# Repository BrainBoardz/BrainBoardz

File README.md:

### 

## BRAINBOARDZ - PLUG and CODE! 

This is the official repository for the BrainBoardz BZBoard system. BZBoards are ESP32-S3 and RP2350B based video (DVI/VGA) and audio centric microcontroller computers. They support Arduino, CircuitPython, MicroPython, AnnexRDS and PlatformIO. Our mission is to empower designers to develop projects based on our advanced and powerful microcontroller architecture. The entire BrainBoardz system is fully documented abd open source. The PCB designs and schematics for all BrainBoardz hardware is released under the CERN-OHL-W V2 license. All software and firmware is released under the GNU GPLv3 License. 

Through the use of our expanding range of cross compatible modules and easy prototyping boards anyone can easily develop custom projects to harness the impressive capabilities of the Raspberry Pi RP2350B and the Espressif ESP32-S3. The boards are specifically designed to be easily adaptable to retro-PC projects. Simply connect one of our ESP32-S3 or RP235OB boards to a USB cable and you are ready to go. 

We do not permit 3rd party board developers to use our logo/branding (as per CERN-OHL-W V2), but you are welcome to indicate that your project is BrainBoardz compatible if it is 100% (pin) compatible and it is produced using lead free solder.  The PCB designs and schematics for all BrainBoardz hardware is released under the CERN-OHL-W V2 license. All software and firmware is released under the GNU GPLv3 License. 

***

Firmware Notes: 

The ESP32S3 Zushi board supports Arduino and AnnexRDS. The RP2350B Beanz board supports CircuitPython, Micropython, Arduino and PlaformIO. For further instructions on these platforms please visit the Downloads page of the BrainBoardz website at:

https://www.brainboardz.com/downloads/

Plug and Code! 

<!--
**BrainBoardz/BrainBoardz** is a ✨ _special_ ✨ repository because its `README.md` (this file) appears on your GitHub profile.

-->

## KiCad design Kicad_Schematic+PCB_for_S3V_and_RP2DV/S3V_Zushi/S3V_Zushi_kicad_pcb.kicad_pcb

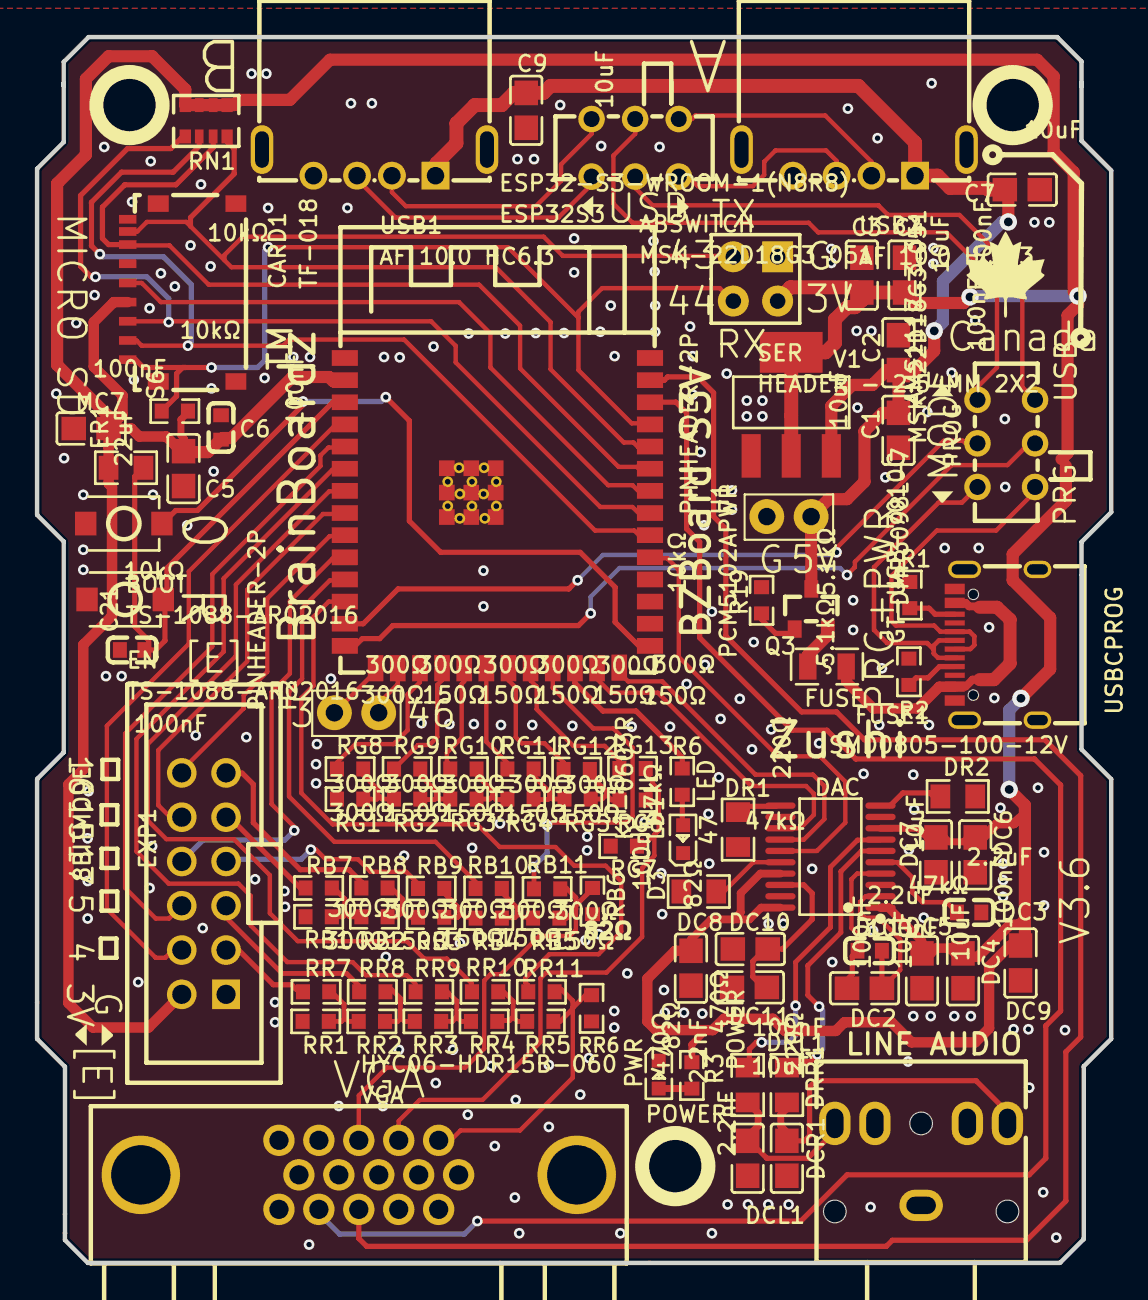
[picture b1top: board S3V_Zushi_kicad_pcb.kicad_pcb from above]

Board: 2 copper layers, 61.6 x 70.3 mm, 107 parts (0 on the bottom side), 84 nets.

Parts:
ABSWITCH: MSK-22D18G3 051; SW-TH_HX-MSK-22D18G3-051
AUS: PJ-3062-G; AUDIO-TH_PJ-3062-G
BOOT: TS-1088-AR02016; SW-SMD_L3.9-W3.0-P4.45
C1, C3, C7, C9: 10uF; C0805
C2, C4: 100nF; C0805
C5: 22uF; C0805
C6, C21: 100nF; C0603
CARD1: TF-018; TF-SMD_TF-018
D3: 47kΩ; R0805
DAC: PCM5102APWR; TSSOP-20_L6.5-W4.4-P0.65-LS6.4-BL
DC1, DC3: 2.2uF; C0603
DC2, DC5, DC7, DC8, DC10: 100nF; C0805
DC4, DC6, DC9, DC11: 10uF; C0805
DCL1: 2.2nF; C0805
DCR1: 2.2nF; C0805
DR1, DR2: 47kΩ; R0805
DRL1: 470Ω; R0805
DRR1: 470Ω; R0805
EN: TS-1088-AR02016; SW-SMD_L3.9-W3.0-P4.45
ER1: 10kΩ; R0805
ESP32S3: ESP32-S3-WROOM-1(N8R8); WIRELM-SMD_ESP32-S3-WROOM-1
EXP1: 8BITMODE; IDC-TH_12P-P2.54_BOOMELE-2X6P-2.54MM
FUSE1: SMD0805-100-12V; F0805
H1, H2: PINHEADER-2P; CONNECTOR_PINHEADER_2.54MM{colon}PINHEADER_1X11_P_2.54MM
Hole_gge1593659: Hole_gge1593659
Hole_gge2213095: Hole_gge2213095
Hole_gge3207251: Hole_gge3207251
LD1: KT-0603R; LED0603-RD
MC7: 100nF; C0805
PROG: MSK-22D18G3 051; SW-TH_HX-MSK-22D18G3-051
PWR: POWER; LED0603-RD
Pad_gge1239083: Pad_gge1239083
Pad_gge1239086: Pad_gge1239086
Pad_gge1239089: Pad_gge1239089
Pad_gge1239092: Pad_gge1239092
Pad_gge1239095: Pad_gge1239095
Pad_gge1239098: Pad_gge1239098
Pad_gge1239101: Pad_gge1239101
Pad_gge1239104: Pad_gge1239104
Pad_gge1239107: Pad_gge1239107
Pad_gge1239110: Pad_gge1239110
Pad_gge1239113: Pad_gge1239113
Pad_gge1239116: Pad_gge1239116
Q3: DMP3098L-7; SOT-23_L2.9-W1.3-P1.90-LS2.4-BR
R1, R2: 5.1kΩ; R0603
R3, R6: 220Ω; R0603
R19: 10kΩ; R0603
RB1, RB7, RB8, RB9, RB10, RB11: 300Ω; R0603
RB2, RB3, RB4, RB5: 150Ω; R0603
RB6: 82Ω; R0603
RG1, RG8, RG9, RG10, RG11, RG12, RG13: 300Ω; R0603
RG2, RG3, RG4, RG5, RG6: 150Ω; R0603
RG7: 82Ω; R0603
RN1: 10kΩ; RES-ARRAY-SMD_0603-8P-L3.2-W1.6-BL
RR1, RR7, RR8, RR9, RR10, RR11: 300Ω; R0603
RR2, RR3, RR4, RR5: 150Ω; R0603
RR6: 82Ω; R0603
S6: 10kΩ; R0603
SER: HEADER - 2.54MM 2X2; 2X2X2.54MM HEADER
USB1, USB2: AF 10.0 HC6.3; USB-A-TH_AF-10.0-HC6.3
USBCPROG: GT-USB-7010C; USB-C-SMD_GT-USB-7010C
V1: AMS1117-3.3; SOT-223-3_L6.5-W3.4-P2.30-LS7.0-BR
VGA: HYC06-HDR15B-060; DSUB-TH_HYC06-HDR15B-060

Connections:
3.3V: C3.2, C4.2, C5.2, C6.2, CARD1.4, DAC.1, DAC.8, DAC.17, DAC.20, DC4.2, DC5.2, DC6.2, DC7.1, DC8.2, DC9.2, ER1.2, ESP32S3.2, EXP1.2, MC7.2, R3.1, RN1.1, RN1.2, RN1.3, RN1.4, S6.2, SER.3, V1.2, V1.4
+5V: C1.2, C2.2, C7.1, C9.1, H1.2, Q3.3, USB1.1, USB2.1, V1.3
AD+: ABSWITCH.1, USB2.3
AD-: ABSWITCH.4, USB2.2
BD+: ABSWITCH.3, USB1.3
BD-: ABSWITCH.6, USB1.2
BLUE: RB5.2, RB6.1, RB11.2, VGA.3
BOOT: BOOT.1, ESP32S3.27
D1+: PROG.4, USBCPROG.A6, USBCPROG.B6
D1-: PROG.1, USBCPROG.A7, USBCPROG.B7
D3_2: D3.2, DAC.16
DC2_1: DAC.4, DC1.1, DC2.1
DC2_2: DAC.2, DC1.2, DC2.2
DC3_1: DAC.5, DC3.1
DC10_1: DAC.18, DC10.1, DC11.1
DR1_2: DAC.11, DR1.2
DR2_2: DAC.10, DR2.2
EN: C21.1, EN.1, ER1.1, ESP32S3.3
G3: ESP32S3.15, H2.1
G4: ESP32S3.4, EXP1.4
G4VGA: EXP1.3, RR7.1
G5: ESP32S3.5, EXP1.6
G5VGA: EXP1.5, RR8.1
G6: ESP32S3.6, RR9.1
G7: ESP32S3.7, RR10.1
G8: ESP32S3.12, RR11.1
G9: ESP32S3.17, RG8.1
G10: ESP32S3.18, RG9.1
G11: ESP32S3.19, RG10.1
G12: ESP32S3.20, RG11.1
G13: ESP32S3.21, RG12.1
G14: ESP32S3.22, RG13.1
G15: ESP32S3.8, EXP1.10
G15VGA: EXP1.9, RB7.1
G16: ESP32S3.9, EXP1.12
G16VGA: EXP1.11, RB8.1
G17: ESP32S3.10, EXP1.8
G17VGA: EXP1.7, RB9.1
G18: ESP32S3.11, RB10.1
G19: ESP32S3.13, PROG.2
G20: ESP32S3.14, PROG.5
G21: ESP32S3.23, RB11.1
G38: DAC.15, ESP32S3.31
G39: CARD1.2, ESP32S3.32, RN1.6
G40: CARD1.3, ESP32S3.33, RN1.5
G41: CARD1.5, ESP32S3.34
G42: CARD1.7, ESP32S3.35, RN1.7
G43: CARD1.8, ESP32S3.36, RN1.8, SER.2
G44: CARD1.1, ESP32S3.37, S6.1, SER.4
G45: DAC.14, ESP32S3.26
G46: ESP32S3.16, H2.2
G47: ESP32S3.24, R6.1
G48: DAC.13, ESP32S3.25
GND: AUS.1, BOOT.2, C1.1, C2.1, C3.1, C4.1, C5.1, C6.1, C7.2, C9.2, C21.2, CARD1.6, CARD1.10, DAC.3, DAC.9, DAC.12, DAC.19, DC3.2, DC4.1, DC5.1, DC6.1, DC7.2, DC8.1, DC9.1, DC10.2, DC11.2, DCL1.1, DCR1.1, DR1.1, DR2.1, EN.2, ESP32S3.1, ESP32S3.40, ESP32S3.41, EXP1.1, H1.1, LD1.1, MC7.1, PWR.1, Pad_gge1239083.43, Pad_gge1239086.43, Pad_gge1239089.43, Pad_gge1239092.43, Pad_gge1239095.43, Pad_gge1239098.43, Pad_gge1239101.43, Pad_gge1239104.43, Pad_gge1239107.43, Pad_gge1239110.43, Pad_gge1239113.43, Pad_gge1239116.43, R1.2, R2.2, R19.2, RB1.1, RB6.2, RG1.1, RG7.2, RR1.1, RR6.2, SER.1, USB1.4, USB1.5, USB1.6, USB2.4, USB2.5, USB2.6, USBCPROG.1, USBCPROG.2, USBCPROG.3, USBCPROG.4, USBCPROG.A1B12, USBCPROG.B1A12, V1.1, VGA.5, VGA.6, VGA.7, VGA.8, VGA.10, VGA.16, VGA.17
GREEN: RG6.2, RG7.1, RG13.2, VGA.2
HSYNC: ESP32S3.39, VGA.13
OUTL: AUS.2, DCL1.2, DRL1.1
OUTLS: DAC.6, DRL1.2
OUTR: AUS.5, DCR1.2, DRR1.1
OUTRS: DAC.7, DRR1.2
Q3_1: Q3.1, R19.1
R3_2: PWR.2, R3.2
R6_2: LD1.2, R6.2
RB1_2: RB1.2, RB2.1, RB7.2
RB2_2: RB2.2, RB3.1, RB8.2
RB3_2: RB3.2, RB4.1, RB9.2
RB4_2: RB4.2, RB5.1, RB10.2
RED: RR5.2, RR6.1, RR11.2, VGA.1
RG1_2: RG1.2, RG2.1, RG8.2
RG2_2: RG2.2, RG3.1, RG9.2
RG3_2: RG3.2, RG4.1, RG10.2
RG4_2: RG4.2, RG5.1, RG11.2
RG5_2: RG5.2, RG6.1, RG12.2
RR1_2: RR1.2, RR2.1, RR7.2
RR8_2: RR2.2, RR3.1, RR8.2
RR9_2: RR3.2, RR4.1, RR9.2
RR10_2: RR4.2, RR5.1, RR10.2
UD+: ABSWITCH.2, PROG.6
UD-: ABSWITCH.5, PROG.3
USBCPROG_A5: R2.1, USBCPROG.A5
USBCPROG_B5: R1.1, USBCPROG.B5
VSYNC: ESP32S3.38, VGA.14
VUSB: FUSE1.1, USBCPROG.A4B9, USBCPROG.B4A9
VUSBPF: FUSE1.2, Q3.2

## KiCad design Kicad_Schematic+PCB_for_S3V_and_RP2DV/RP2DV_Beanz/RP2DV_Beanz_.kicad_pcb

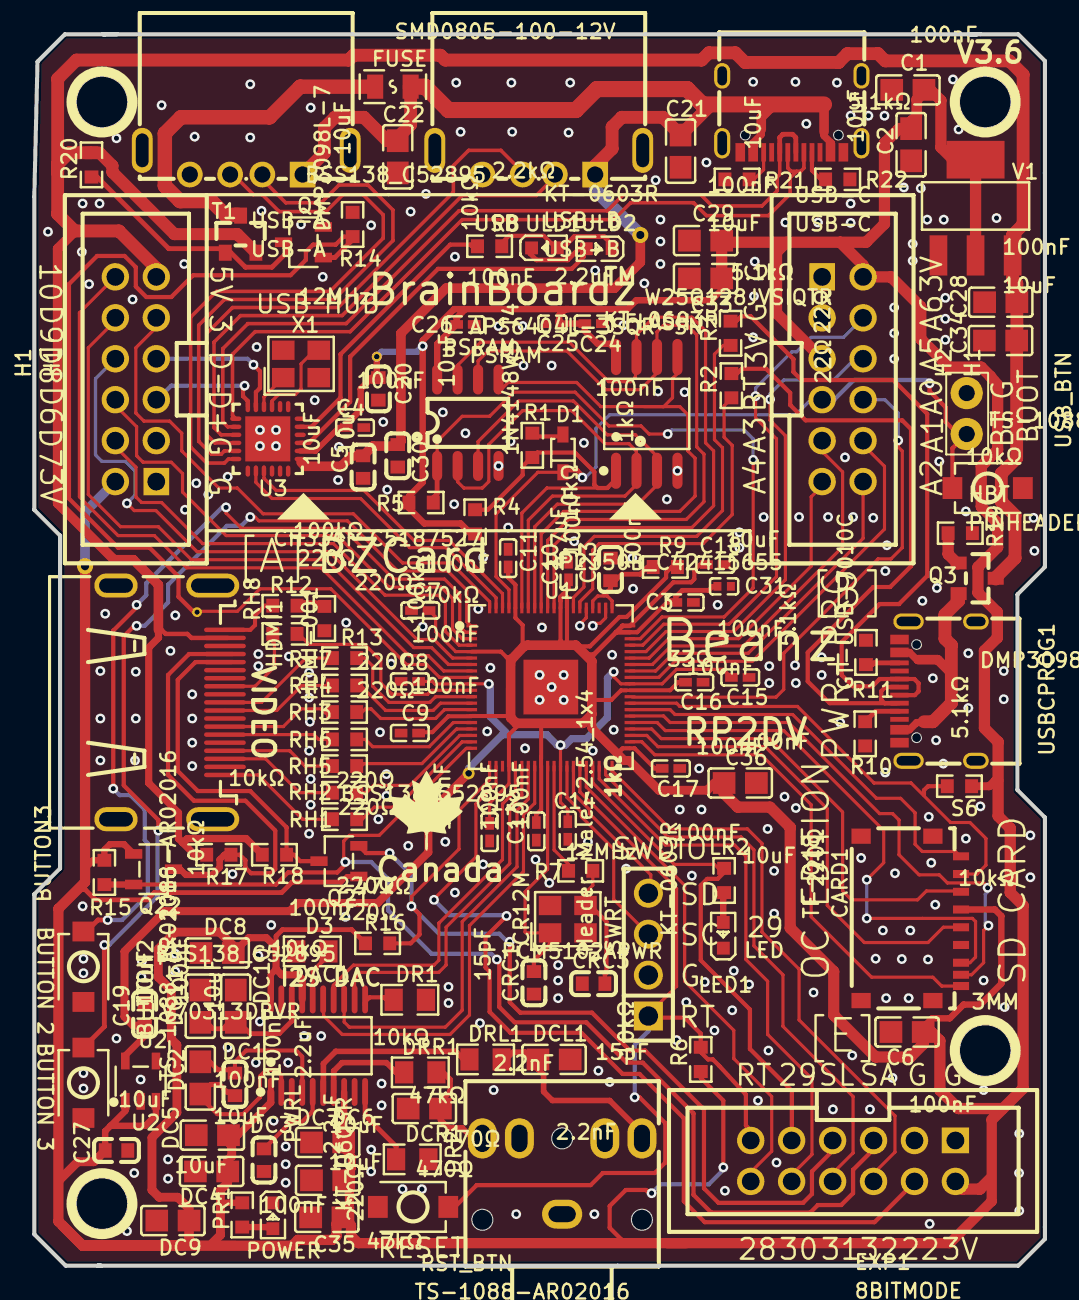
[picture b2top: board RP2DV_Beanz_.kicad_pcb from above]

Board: 2 copper layers, 62.7 x 76.4 mm, 133 parts (0 on the bottom side), 116 nets.

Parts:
AUS1: PJ-3062-G; AUDIO-TH_PJ-3062-G
BUTTON2, BUTTON3: TS-1088-AR02016; SW-SMD_L3.9-W3.0-P4.45
C1, C6, C29, C34: 100nF; C0805
C2, C21, C22, C28, C33, C35, C36: 10uF; C0805
C3, C4, C7, C8, C9, C10, C11, C12, C13, C14, C15, C16, C17, C18, C24, C26: 100nF; C0402
C5, C19, C20, C27, C30: 10uF; C0603
C23: 4.7uF; C0603
C25: 2.2uF; C0402
C31: 10uF; C0402
CARD1: TF-018; TF-SMD_TF-018
CR12M: 12MHz; CRYSTAL-SMD_4P-L3.2-W2.5-BL
CRC1, CRC3: 15pF; C0603
D1: 1N4148WS T4; SOD-323_L1.8-W1.3-LS2.5-RD
D3: 47kΩ; R0805
DAC1: PCM5102APWR; TSSOP-20_L6.5-W4.4-P0.65-LS6.4-BL
DC1, DC3: 2.2uF; C0603
DC2, DC5, DC7, DC8, DC10: 100nF; C0805
DC4, DC6, DC9, DC11: 10uF; C0805
DCL1: 2.2nF; C0805
DCR1: 2.2nF; C0805
DR1, DR2: 47kΩ; R0805
DRL1: 470Ω; R0805
DRR1: 470Ω; R0805
EXP1: 8BITMODE; IDC-TH_12P-P2.54_BOOMELE-2X6P-2.54MM
FLASH: W25Q128JVSIQTR; SOIC-8_L5.3-W5.3-P1.27-LS8.0-BL
FUSE: SMD0805-100-12V; F0805
H1, H2: H1; IDC-TH_12P-P2.54_BOOMELE-2X6P-2.54MM
HBT: PINHEADER-2P; CONNECTOR_PINHEADER_2.54MM{colon}PINHEADER_1X11_P_2.54MM
HDMI1: HDMI-001; HDMI-SMD_19P-P0.50-H-F
Hole_gge3727755: Hole_gge3727755
Hole_gge3727770: Hole_gge3727770
Hole_gge3727785: Hole_gge3727785
Hole_gge3727818: Hole_gge3727818
LED1: KT-0603R; LED0603-RD
LR2: 220Ω; R0603
PR1: 220Ω; R0603
PSRAM: APS6404L-3SQR-SN; SOP-8_L4.9-W3.9-P1.27-LS6.0-BL
PWRL: KT-0603R; LED0603-RD
Pad_gge2986524: Pad_gge2986524
Pad_gge3015517: Pad_gge3015517
Pad_gge3860084: Pad_gge3860084
Pad_gge3861164: Pad_gge3861164
Pad_gge4051184: Pad_gge4051184
Q1, Q21, Q22: BSS138_C52895; SOT-23-3_L2.9-W1.6-P1.90-LS2.8-BR
Q3: DMP3098L-7; SOT-23_L2.9-W1.3-P1.90-LS2.4-BR
R1, R7: 1kΩ; R0603
R2, R3: 22Ω; R0603
R4, R5, R6, R14, R15, R16, R17, R18, R19, R20: 10kΩ; R0603
R8: 2.2kΩ; R0603
R9: 33Ω; R0603
R10, R11, R21, R22: 5.1kΩ; R0603
R12, R13: 100kΩ; R0603
RH1, RH2, RH3, RH4, RH5, RH6, RH7, RH8: 220Ω; R0603
RST_BTN: TS-1088-AR02016; SW-SMD_L3.9-W3.0-P4.45
S6: 10kΩ; R0603
SWRT: Header-Male-2.54_1x4; DIP-1X4P-2.54MM-M
T1: DMP3098L-7; SOT-23_L2.9-W1.3-P1.90-LS2.4-BR
U1: RP2350B_C42415655; QFN-80_L10.0-W10.0-P0.40-TL-EP3.4
U2: TLV70313DBVR; SOT-23-5_L3.0-W1.6-P0.95-LS2.8-BR
U3: CH334F_C5187527; QFN-24_L4.0-W4.0-P0.50-BL-EP2.8
ULD1, ULD2: KT-0603R; LED0603-RD
USB-A: USB-A; USB-A-TH_AF-10.0-HC6.3
USB-B: USB-B; USB-A-TH_AF-10.0-HC6.3
USB-C: USB-C; USB-C-SMD_GT-USB-7010C
USBCPROG1: GT-USB-7010C; USB-C-SMD_GT-USB-7010C
USB_BTN: TS-1088-AR02016; SW-SMD_L3.9-W3.0-P4.45
V1: AMS1117-3.3; SOT-223-3_L6.5-W3.4-P2.30-LS7.0-BR
X1: 12MHz; CRYSTAL-SMD_4P-L3.2-W2.5-BL

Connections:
1.3V: C8.2, C14.2, C15.2, C19.2, U1.10, U1.32, U1.51, U2.5
3.3V: C1.2, C2.2, C3.2, C4.1, C6.1, C7.2, C9.2, C10.2, C11.2, C12.2, C13.2, C16.2, C17.2, C18.2, C20.1, C24.2, C25.2, C26.1, C27.1, C29.2, C31.1, C33.2, C35.2, C36.2, CARD1.4, DAC1.1, DAC1.8, DAC1.17, DAC1.20, DC4.2, DC5.2, DC6.2, DC7.1, DC8.2, DC9.2, EXP1.2, FLASH.8, H1.2, H2.2, H2.5, PR1.1, PSRAM.8, Q21.1, Q22.1, R4.2, R5.2, R6.1, R9.1, R15.1, R16.2, S6.1, U1.5, U1.15, U1.24, U1.29, U1.41, U1.50, U1.59, U1.60, U1.68, U1.69, U1.76, U2.1, U2.3, U3.20, V1.2, V1.4
5V: C28.2, C34.2, H1.11, HDMI1.18, Q3.3, R17.1, R18.2, R20.2, T1.2, V1.3
A0: H2.8, U1.49
A1: H2.10, U1.52
A2: H2.12, U1.53
A3: H2.9, U1.54
A4: H2.11, U1.55
A5: H2.6, U1.56
A6: H2.4, U1.57
D6: H1.6, U1.3
D7: H1.4, U1.4
D8_TX1: H1.8, U1.6
D9_RX1: H1.10, U1.7
D10: H1.12, U1.8
D+: R2.2, U1.67
D+1: U3.12, USB-A.3
D+2: U3.10, USB-B.3
D+3: U3.8, USB-C.A6, USB-C.B6
D+4: H1.5, U3.6
D-: R3.2, U1.66
D-1: U3.11, USB-A.2
D-2: U3.9, USB-B.2
D-3: U3.7, USB-C.A7, USB-C.B7
D-4: H1.7, U3.5
DAC1_2: DAC1.2, DC1.2, DC2.2
DAC1_4: DAC1.4, DC1.1, DC2.1
DAC1_5: DAC1.5, DC3.1
DAC1_10: DAC1.10, DR2.2
DAC1_11: DAC1.11, DR1.2
DAC1_16: D3.2, DAC1.16
DC11_1: DAC1.18, DC10.1, DC11.1
GND: AUS1.1, BUTTON2.2, BUTTON3.2, C1.1, C2.1, C3.1, C4.2, C5.1, C6.2, C7.1, C8.1, C9.1, C10.1, C11.1, C12.1, C13.1, C14.1, C15.1, C16.1, C17.1, C18.1, C19.1, C20.2, C21.2, C22.1, C23.2, C24.1, C25.1, C26.2, C27.2, C28.1, C29.1, C30.1, C31.2, C33.1, C34.1, C35.1, C36.1, CARD1.6, CARD1.10, CR12M.2, CR12M.4, CRC1.1, CRC3.2, DAC1.3, DAC1.9, DAC1.19, DC3.2, DC4.1, DC5.1, DC6.1, DC7.2, DC8.1, DC9.1, DC10.2, DC11.2, DCL1.1, DCR1.1, DR1.1, DR2.1, EXP1.1, EXP1.3, FLASH.4, H1.1, H1.3, H2.1, H2.3, HBT.2, HDMI1.2, HDMI1.5, HDMI1.8, HDMI1.11, HDMI1.17, HDMI1.20, HDMI1.21, HDMI1.22, HDMI1.23, LED1.1, PSRAM.4, PWRL.1, Q1.2, R10.2, R11.2, R13.2, R14.1, R19.2, R21.2, R22.2, RST_BTN.2, SWRT.2, U1.62, U1.65, U1.81, U2.2, U3.25, USB-A.4, USB-A.5, USB-A.6, USB-B.4, USB-B.5, USB-B.6, USB-C.1, USB-C.2, USB-C.3, USB-C.4, USB-C.A1B12, USB-C.B1A12, USBCPROG1.1, USBCPROG1.2, USBCPROG1.3, USBCPROG1.4, USBCPROG1.A1B12, USBCPROG1.B1A12, USB_BTN.2, V1.1, X1.2, X1.4
GPIO3: H1.9, U1.80
GPIO4: BUTTON2.1, U1.1
GPIO5: BUTTON3.1, U1.2
GPIO22: EXP1.4, U1.22
GPIO28: EXP1.12, U1.36
GPIO30: EXP1.10, U1.38
GPIO31: EXP1.8, U1.39
GPIO32: EXP1.6, U1.40
HDMI1_1: HDMI1.1, RH1.2
HDMI1_3: HDMI1.3, RH2.2
HDMI1_4: HDMI1.4, RH5.1
HDMI1_6: HDMI1.6, RH6.1
HDMI1_7: HDMI1.7, RH3.2
HDMI1_9: HDMI1.9, RH4.2
HDMI1_10: HDMI1.10, RH7.1
HDMI1_12: HDMI1.12, RH8.1
HDMI1_19: HDMI1.19, R12.1
HDMI-SCL: HDMI1.15, Q21.3, R18.1
HDMI-SDA: HDMI1.16, Q22.3, R17.2
HOTPLUG_3V: R12.2, R13.1
HSTX12: RH8.2, U1.11
HSTX13: RH7.2, U1.12
HSTX14: RH4.1, U1.13
HSTX15: RH3.1, U1.14
HSTX16: RH6.2, U1.16
HSTX17: RH5.2, U1.17
HSTX18: RH2.1, U1.18
HSTX19: RH1.1, U1.19
I2S_BCLK: DAC1.13, U1.27
I2S_DIN: DAC1.14, U1.25
I2S_LRCLK: DAC1.15, U1.28
I2S_MCLK: DAC1.12, U1.26
LED: EXP1.9, LR2.1, U1.37
LED1_2: LED1.2, LR2.2
LED2: R8.1, U3.23
LED4: U3.21, ULD1.1, ULD2.2
MISO/SDIO_DAT0: CARD1.7, U1.45
MOSI/SDIO_CMD: CARD1.3, U1.44
OUTL: AUS1.2, DCL1.2, DRL1.1
OUTLS: DAC1.6, DRL1.2
OUTR: AUS1.5, DCR1.2, DRR1.1
OUTRS: DAC1.7, DRR1.2
PSRAM_CS: PSRAM.1, R5.1, U1.58
PWRL_2: PR1.2, PWRL.2
Q1_3: Q1.3, R20.1, T1.1
Q3_1: Q3.1, R19.1
QSPI_CS: FLASH.1, R1.2, R4.1, U1.75
QSPI_DATA[0]: FLASH.5, PSRAM.5, U1.72
QSPI_DATA[1]: FLASH.2, PSRAM.2, U1.74
QSPI_DATA[2]: FLASH.3, PSRAM.3, U1.73
QSPI_DATA[3]: FLASH.7, PSRAM.7, U1.70
QSPI_SCK: FLASH.6, PSRAM.6, U1.71
R1_1: D1.2, R1.1
R10_1: R10.1, USBCPROG1.A5
R11_1: R11.1, USBCPROG1.B5
RESET: EXP1.11, R6.2, RST_BTN.1, SWRT.1, U1.35
SCK/SDIO_CLK: CARD1.5, U1.43
SCL: EXP1.7, Q21.2, R16.1, U1.21
SDA: EXP1.5, Q22.2, R15.2, U1.20
SDCS/SDIO_DAT3: CARD1.2, S6.2, U1.48
SDIO_DAT1: CARD1.8, U1.46
SDIO_DAT2: CARD1.1, U1.47
SD_DETECT: CARD1.9, U1.42
SWCLK: SWRT.3, U1.33
SWDIO: SWRT.4, U1.34
T1_3: FUSE.1, T1.3
ULD2_1: R8.2, ULD1.2, ULD2.1
USB-C_A5: R22.1, USB-C.A5
USB-C_B5: R21.1, USB-C.B5
USBH-D+: U1.78, U3.15
USBH-D-: U1.79, U3.14
USBH_PWR: Q1.1, R14.2, U1.9
USB_BOOT: D1.1, H2.7, HBT.1, U1.77, USB_BTN.1
USB_D+: R2.1, USBCPROG1.A6, USBCPROG1.B6
USB_D-: R3.1, USBCPROG1.A7, USBCPROG1.B7
VBUS: C5.2, C21.1, C22.2, C30.2, FUSE.2, U3.19, USB-A.1, USB-B.1, USB-C.A4B9, USB-C.B4A9
VREG-AVDD: C23.1, R9.2, U1.61, U1.64
VUSB: Q3.2, USBCPROG1.A4B9, USBCPROG1.B4A9
XI: U3.4, X1.1
XIN: CR12M.1, CRC1.2, U1.30
XO: U3.3, X1.3
XOUT: CR12M.3, CRC3.1, R7.2
XOUTR: R7.1, U1.31
